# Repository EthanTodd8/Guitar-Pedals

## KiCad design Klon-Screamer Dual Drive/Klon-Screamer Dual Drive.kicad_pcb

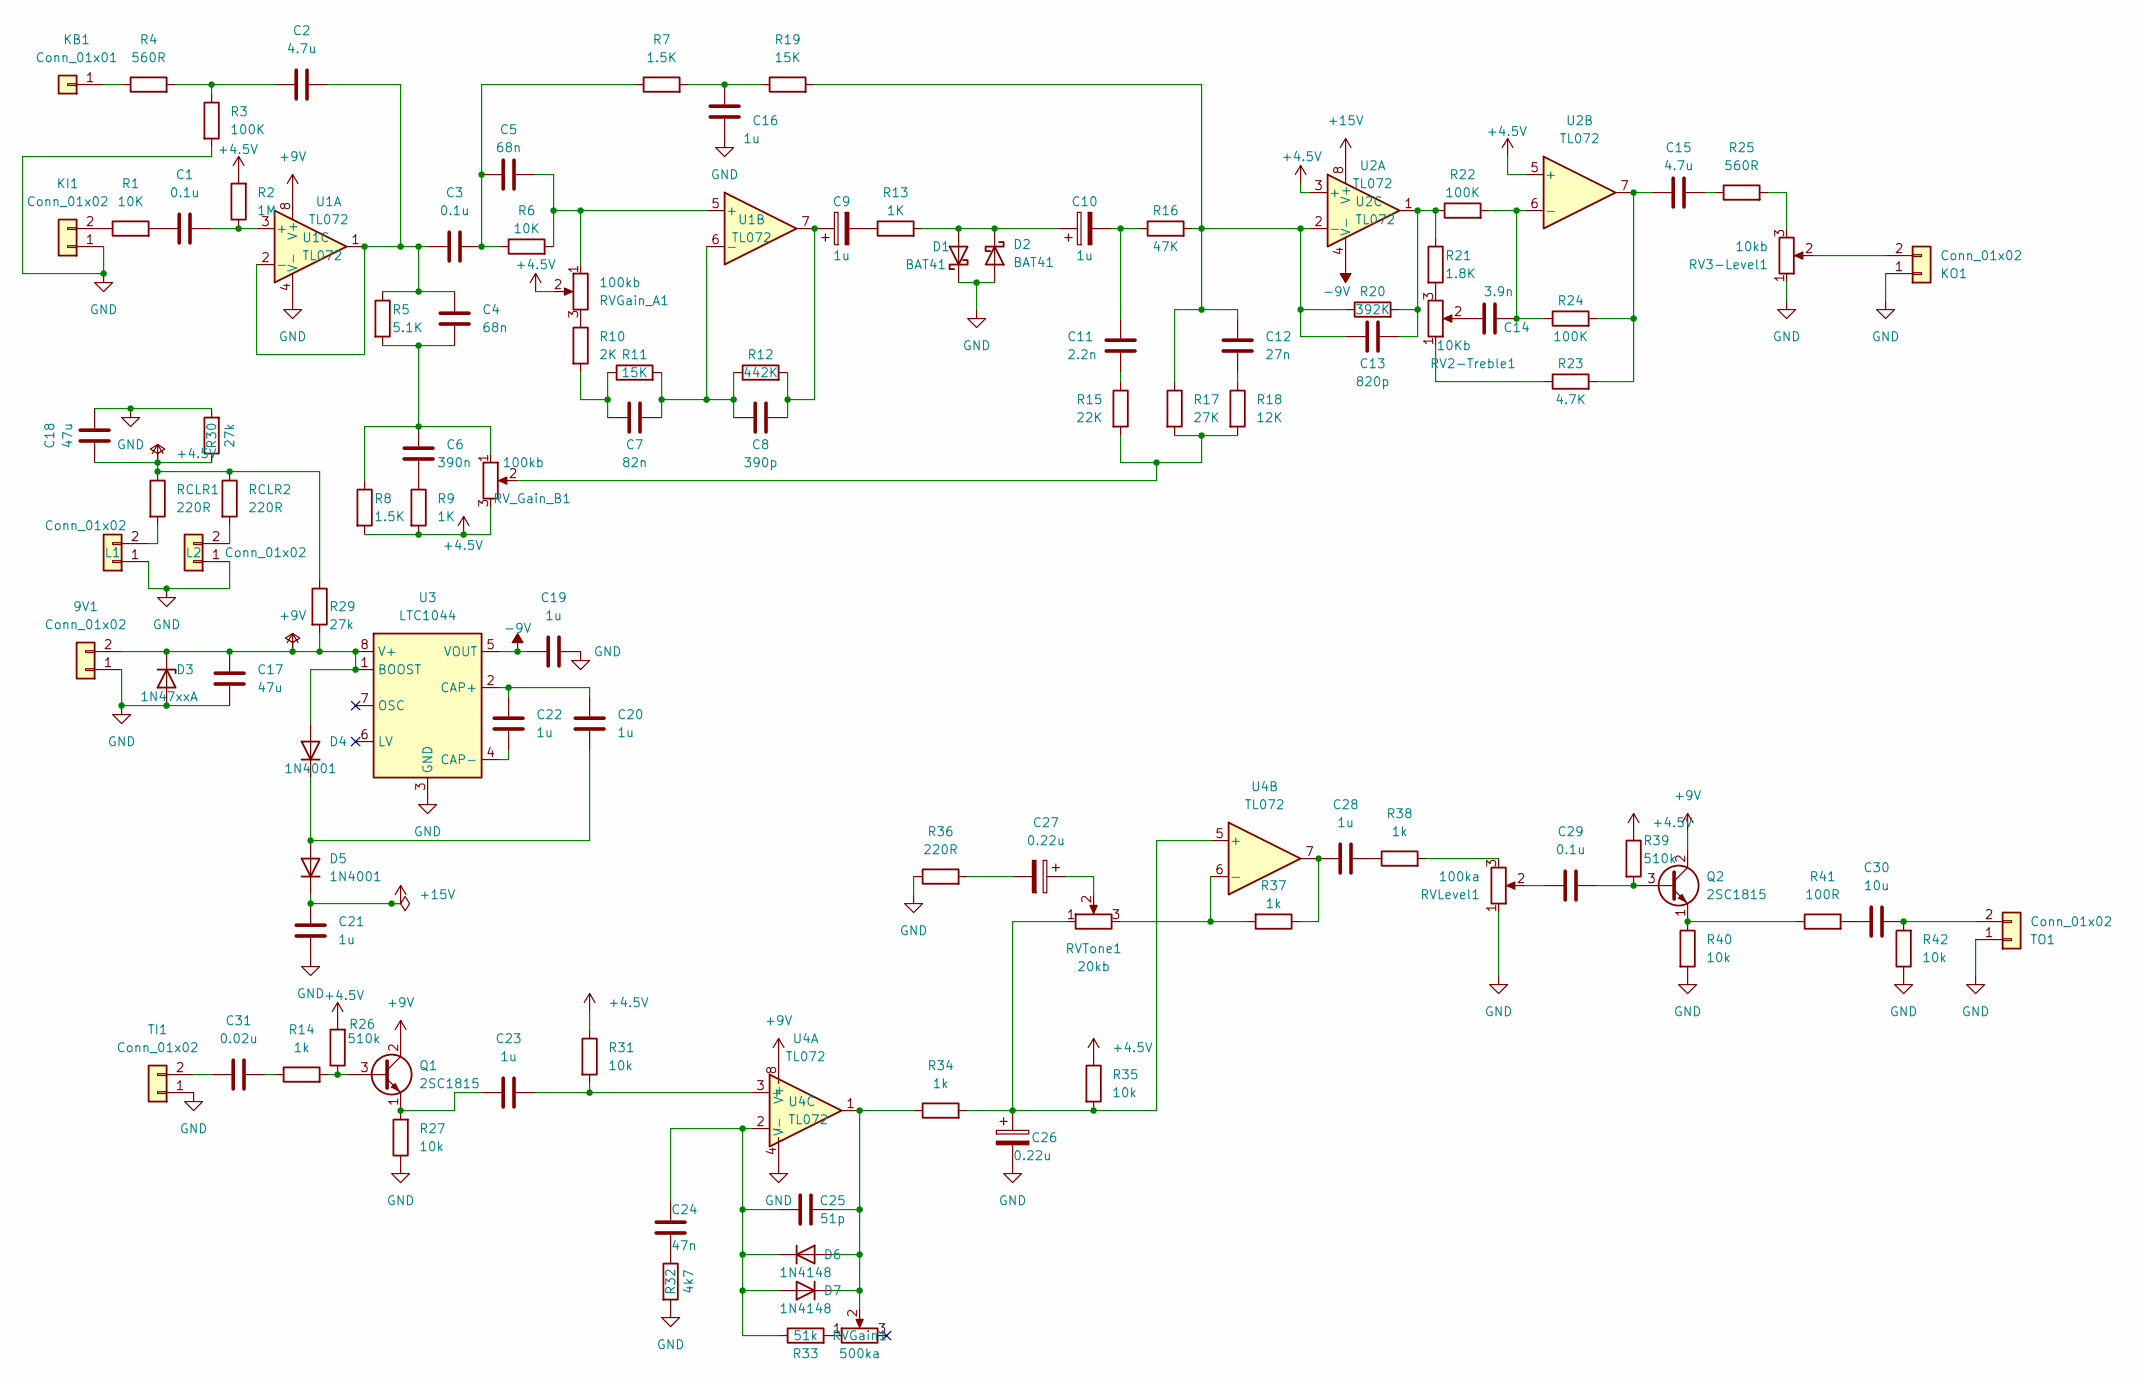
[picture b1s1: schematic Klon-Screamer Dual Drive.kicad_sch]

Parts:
9V1: Conn_01x02; PinHeader_1x02_P2.00mm_Vertical
C1, C3, C29: 0.1u; C_0603_1608Metric
C2, C15: 4.7u; C_Rect_L7.2mm_W7.2mm_P5.00mm_FKS2_FKP2_MKS2_MKP2
C4, C5: 68n; C_0603_1608Metric
C6: 390n; C_0603_1608Metric
C7: 82n; C_0603_1608Metric
C8: 390p; C_0603_1608Metric
C9, C10, C16, C19, C20, C21, C22, C23, C28: 1u; C_0603_1608Metric
C11: 2.2n; C_0603_1608Metric
C12: 27n; C_0603_1608Metric
C13: 820p; C_0603_1608Metric
C14: 3.9n; C_0603_1608Metric
C17, C18: 47u; CP_Radial_D5.0mm_P2.50mm
C24: 47n; C_0603_1608Metric
C25: 51p; C_0603_1608Metric
C26, C27: 0.22u; C_0603_1608Metric
C30: 10u; CP_Radial_D5.0mm_P2.50mm
C31: 0.02u; C_0603_1608Metric
D1, D2: BAT41; D_DO-35_SOD27_P7.62mm_Horizontal
D3: 1N47xxA; D_DO-41_SOD81_P7.62mm_Horizontal
D4, D5: 1N4001; D_DO-41_SOD81_P7.62mm_Horizontal
D6, D7: 1N4148; D_DO-35_SOD27_P7.62mm_Horizontal
KB1: Conn_01x01; PinHeader_1x01_P2.00mm_Vertical
KI1: Conn_01x02; PinHeader_1x02_P2.00mm_Vertical
KO1: Conn_01x02; PinHeader_1x02_P2.00mm_Vertical
L1, L2: Conn_01x02; PinHeader_1x02_P2.00mm_Vertical
Q1, Q2: 2SC1815; TO-92_Inline
R1, R6: 10K; R_0603_1608Metric
R2: 1M; R_0603_1608Metric
R3, R22, R24: 100K; R_0603_1608Metric
R4, R25: 560R; R_0603_1608Metric
R5: 5.1K; R_0603_1608Metric
R7, R8: 1.5K; R_0603_1608Metric
R9, R13: 1K; R_0603_1608Metric
R10: 2K; R_0603_1608Metric
R11, R19: 15K; R_0603_1608Metric
R12: 442K; R_0603_1608Metric
R14, R34, R37, R38: 1k; R_0603_1608Metric
R15: 22K; R_0603_1608Metric
R16: 47K; R_0603_1608Metric
R17: 27K; R_0603_1608Metric
R18: 12K; R_0603_1608Metric
R20: 392K; R_0603_1608Metric
R21: 1.8K; R_0603_1608Metric
R23: 4.7K; R_0603_1608Metric
R26, R39: 510k; R_0603_1608Metric
R27, R31, R35, R40, R42: 10k; R_0603_1608Metric
R29, R30: 27k; R_0603_1608Metric
R32: 4k7; R_0603_1608Metric
R33: 51k; R_0603_1608Metric
R36: 220R; R_0603_1608Metric
R41: 100R; R_0603_1608Metric
RCLR1, RCLR2: 220R; R_0603_1608Metric
RV2-Treble1: 10Kb; Potentiometer_Piher_PC-16_Single_Vertical
RV3-Level1: 10kb; Potentiometer_Piher_PC-16_Single_Vertical
RVGain1: 500ka; Potentiometer_Piher_PC-16_Single_Vertical
RVGain_A1: 100kb; Potentiometer_Piher_PC-16_Single_Vertical
RVLevel1: 100ka; Potentiometer_Piher_PC-16_Single_Vertical
RVTone1: 20kb; Potentiometer_Piher_PC-16_Single_Vertical
RV_Gain_B1: 100kb; Potentiometer_Piher_PC-16_Single_Vertical
TI1: Conn_01x02; PinHeader_1x02_P2.00mm_Vertical
TO1: Conn_01x02; PinHeader_1x02_P2.00mm_Vertical
U1, U2, U4: TL072; DIP-8_W7.62mm
U3: LTC1044; DIP-8_W7.62mm

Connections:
+4V: C18.1, R2.2, R8.2, R9.2, R26.2, R29.1, R30.1, R31.1, R35.1, R39.1, RCLR1.1, RCLR2.1, RVGain_A1.2, RV_Gain_B1.3, U2.3 (+), U2.5 (+)
+9V: 9V1.2, C17.1, D3.1 (K), D4.2 (A), Q1.2 (C), Q2.2 (C), R29.2, U1.8 (V+), U3.1 (BOOST), U3.8 (V+), U4.8 (V+)
+15V: C21.1, D5.1 (K), U2.8 (V+)
-8V: C19.1, U2.4 (V-), U3.5 (VOUT)
GND: 9V1.1, C16.2, C17.2, C18.2, C19.2, C21.2, C26.2, D1.1 (K), D2.2 (A), D3.2 (A), KI1.1, KO1.1, L1.1, L2.1, R3.2, R27.1, R30.2, R32.2, R36.1, R40.2, R42.1, RV3-Level1.1, RVLevel1.1, TI1.1, TO1.1, U1.4 (V-), U3.3 (GND), U4.4 (V-)
unnamed: C1.1, R1.2
unnamed: C2.1, R3.1, R4.2
unnamed: C3.2, C5.1, R6.1, R7.1
unnamed: C4.2, C6.1, R5.2, R8.1, RV_Gain_B1.1
unnamed: C6.2, R9.1
unnamed: C7.2, R10.2, R11.1
unnamed: C8.2, C9.1, R12.2, U1.7
unnamed: C9.2, R13.1
unnamed: C10.2, C11.1, R16.1
unnamed: C11.2, R15.1
unnamed: C12.2, R18.1
unnamed: C13.2, R20.2, R21.1, R22.1, U2.1
unnamed: C14.1, RV2-Treble1.2
unnamed: C15.1, R23.2, R24.2, U2.7
unnamed: C15.2, R25.1
unnamed: C16.1, R7.2, R19.1
unnamed: C24.2, R32.1
unnamed: C27.1, RVTone1.2
unnamed: C27.2, R36.2
unnamed: C28.1, R37.1, U4.7
unnamed: C28.2, R38.1
unnamed: C29.1, RVLevel1.2
unnamed: C30.1, R41.2
unnamed: C31.2, R14.1
unnamed: C10.1, D1.2 (A), D2.1 (K), R13.2
unnamed: C20.2, D4.1 (K), D5.2 (A)
unnamed: C25.2, D6.2 (A), D7.1 (K), R34.1, RVGain1.2, U4.1
unnamed: C24.1, C25.1, D6.1 (K), D7.2 (A), R33.1, U4.2 (-)
unnamed: KB1.1, R4.1
unnamed: KI1.2, R1.1
unnamed: KO1.2, RV3-Level1.2
unnamed: L1.2, RCLR1.2
unnamed: L2.2, RCLR2.2
unnamed: Q1.3 (B), R14.2, R26.1
unnamed: C23.1, Q1.1 (E), R27.2
unnamed: C29.2, Q2.3 (B), R39.2
unnamed: Q2.1 (E), R40.1, R41.1
unnamed: R10.1, RVGain_A1.3
unnamed: R15.2, R17.2, R18.2, RV_Gain_B1.2
unnamed: R21.2, RV2-Treble1.3
unnamed: R23.1, RV2-Treble1.1
unnamed: R25.2, RV3-Level1.3
unnamed: R33.2, RVGain1.1
unnamed: R38.2, RVLevel1.3
unnamed: C31.1, TI1.2
unnamed: C30.2, R42.2, TO1.2
unnamed: C1.2, R2.1, U1.3 (+)
unnamed: C2.2, C3.1, C4.1, R5.1, U1.1, U1.2 (-)
unnamed: C5.2, R6.2, RVGain_A1.1, U1.5 (+)
unnamed: C7.1, C8.1, R11.2, R12.1, U1.6 (-)
unnamed: C12.1, C13.1, R16.2, R17.1, R19.2, R20.1, U2.2 (-)
unnamed: C14.2, R22.2, R24.1, U2.6 (-)
unnamed: C20.1, C22.1, U3.2 (CAP+)
unnamed: C22.2, U3.4 (CAP-)
unnamed: C23.2, R31.2, U4.3 (+)
unnamed: C26.1, R34.2, R35.2, RVTone1.1, U4.5 (+)
unnamed: R37.2, RVTone1.3, U4.6 (-)

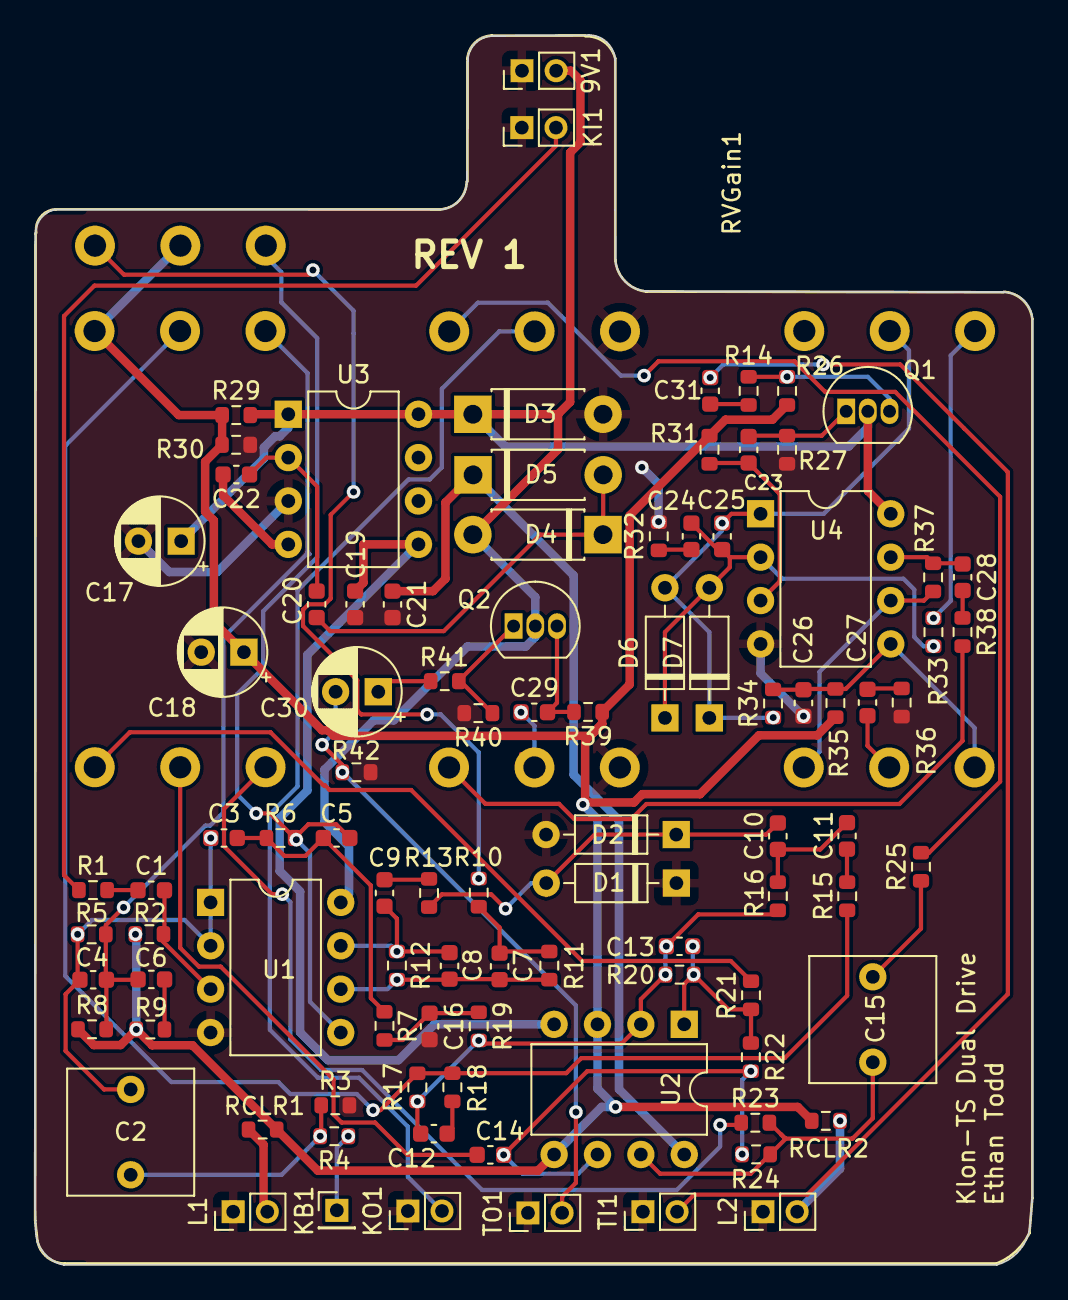
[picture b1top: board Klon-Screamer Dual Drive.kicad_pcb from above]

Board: 2 copper layers, 58.4 x 72.0 mm, 102 parts (0 on the bottom side), 62 nets.

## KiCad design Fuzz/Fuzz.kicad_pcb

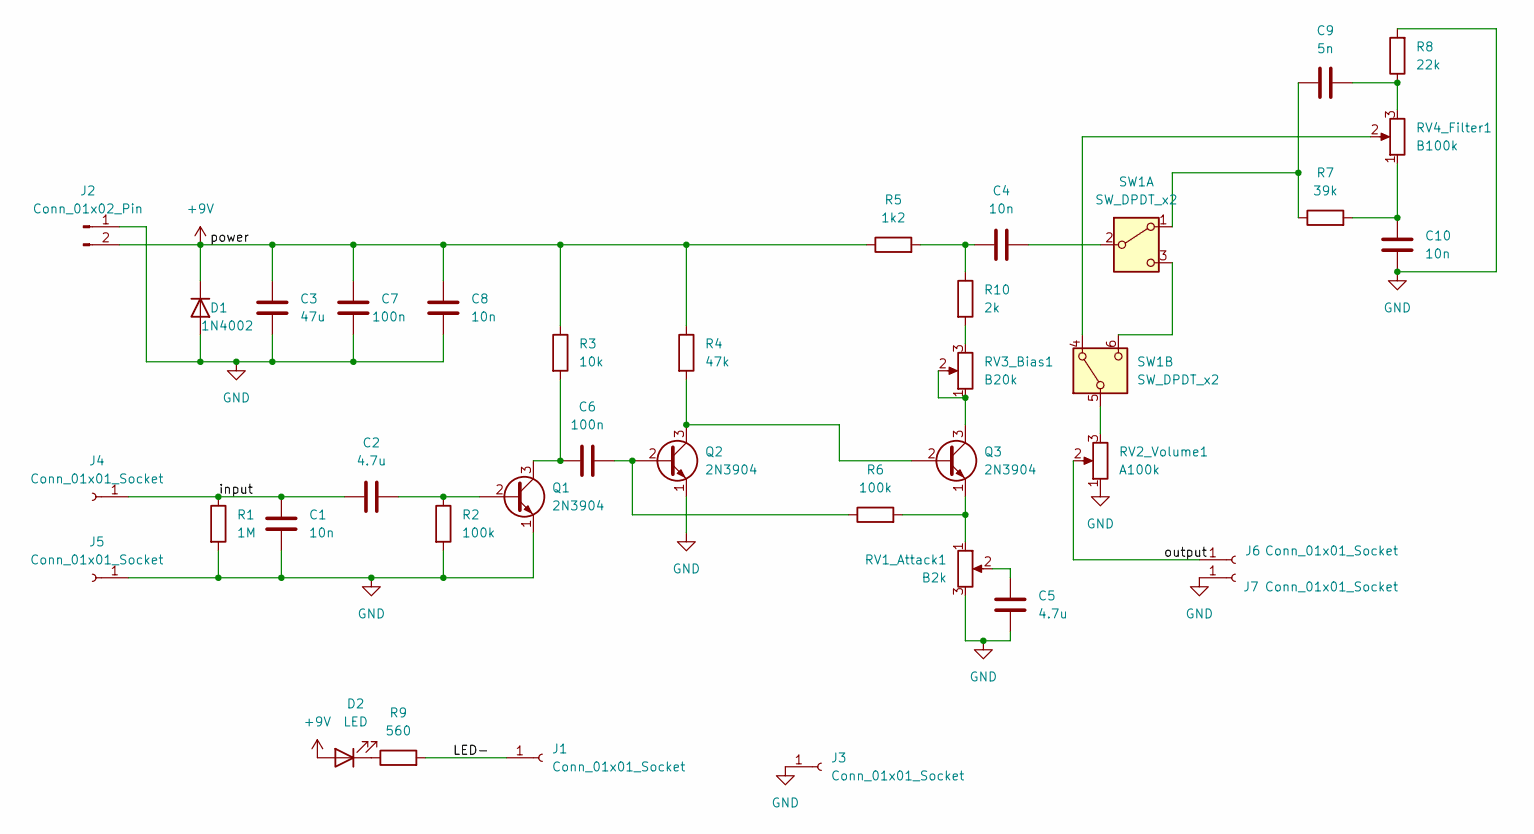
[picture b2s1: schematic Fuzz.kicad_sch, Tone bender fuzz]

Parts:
C1, C4, C8, C10: 10n; C_0603_1608Metric
C2, C5: 4.7u; C_0603_1608Metric
C3: 47u; C_1206_3216Metric
C6, C7: 100n; C_0603_1608Metric
C9: 5n; C_0603_1608Metric
D1: 1N4002; D_DO-41_SOD81_P10.16mm_Horizontal
D2: LED; LED_D3.0mm
J1, J3, J4, J5, J6, J7: Conn_01x01_Socket; PinSocket_1x01_P2.54mm_Vertical
J2: Conn_01x02_Pin; PinSocket_1x02_P2.54mm_Vertical
Q1, Q2, Q3: 2N3904; TO-92_Inline
R1: 1M; R_0603_1608Metric
R2, R6: 100k; R_0603_1608Metric
R3: 10k; R_0603_1608Metric
R4: 47k; R_0603_1608Metric
R5: 1k2; R_0603_1608Metric
R7: 39k; R_0603_1608Metric
R8: 22k; R_0603_1608Metric
R9: 560; R_0603_1608Metric
R10: 2k; R_0603_1608Metric
RV1_Attack1: B2k; Potentiometer_Piher_PC-16_Single_Vertical
RV2_Volume1: A100k; Potentiometer_Piher_PC-16_Single_Vertical
RV3_Bias1: B20k; Potentiometer_Piher_PC-16_Single_Vertical
RV4_Filter1: B100k; Potentiometer_Piher_PC-16_Single_Vertical
SW1: SW_DPDT_x2; DPDT

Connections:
+9V: C3.1, C7.1, C8.1, D1.1 (K), D2.2 (A), J2.2, R3.1, R4.1, R5.1
/LED-: J1.1, R9.2
/input: C1.1, C2.1, J4.1, R1.1
/output: J6.1, RV2_Volume1.2
GND: C1.2, C3.2, C5.2, C7.2, C8.2, C10.2, D1.2 (A), J2.1, J3.1, J5.1, J7.1, Q1.1 (E), Q2.1 (E), R1.2, R2.2, R8.2, RV1_Attack1.3, RV2_Volume1.1
unnamed: C4.2, R5.2, R10.1
unnamed: C5.1, RV1_Attack1.2
unnamed: C9.2, R8.1, RV4_Filter1.3
unnamed: C10.1, R7.2, RV4_Filter1.1
unnamed: D2.1 (K), R9.1
unnamed: C2.2, Q1.2 (B), R2.1
unnamed: C6.1, Q1.3 (C), R3.2
unnamed: C6.2, Q2.2 (B), R6.1
unnamed: Q2.3 (C), Q3.2 (B), R4.2
unnamed: Q3.3 (C), RV3_Bias1.1, RV3_Bias1.2
unnamed: Q3.1 (E), R6.2, RV1_Attack1.1
unnamed: R10.2, RV3_Bias1.3
unnamed: C9.1, R7.1, SW1.1 (A)
unnamed: C4.1, SW1.2 (B)
unnamed: SW1.3 (C), SW1.6 (C)
unnamed: RV4_Filter1.2, SW1.4 (A)
unnamed: RV2_Volume1.3, SW1.5 (B)

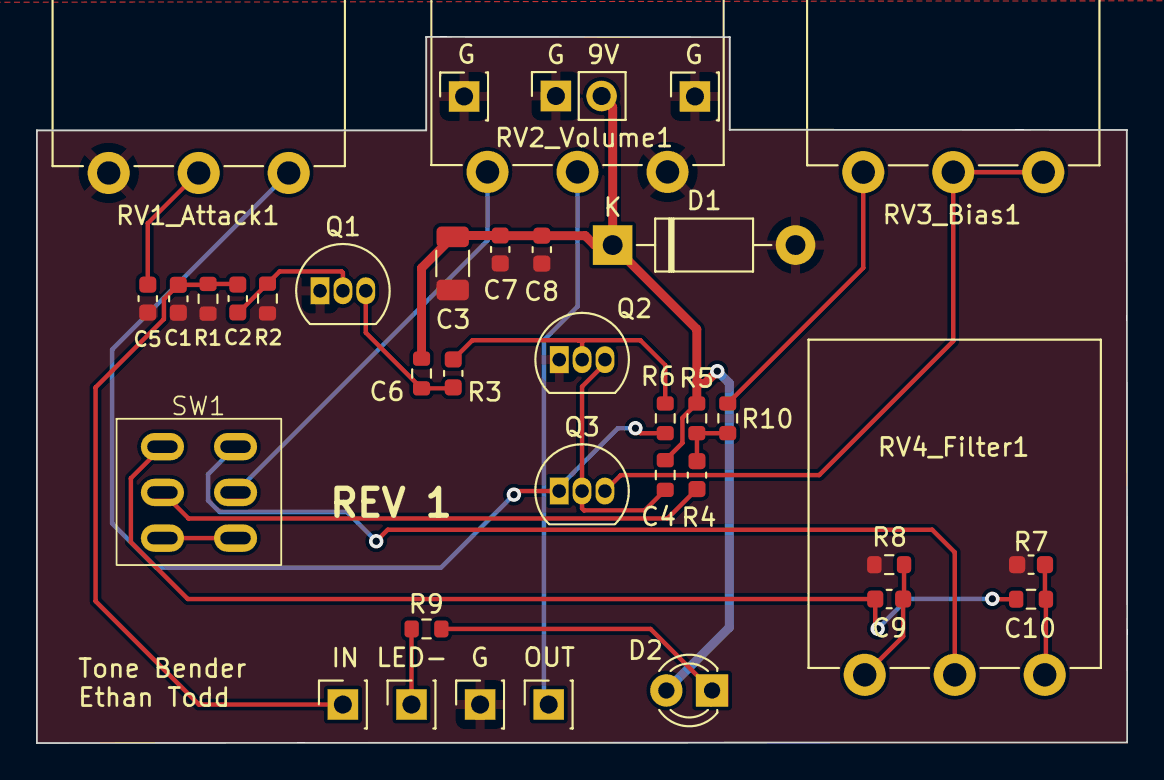
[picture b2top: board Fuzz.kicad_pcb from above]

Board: 2 copper layers, 60.6 x 39.2 mm, 37 parts (0 on the bottom side), 22 nets.

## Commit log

2024-04-19 Ordered PCBs
